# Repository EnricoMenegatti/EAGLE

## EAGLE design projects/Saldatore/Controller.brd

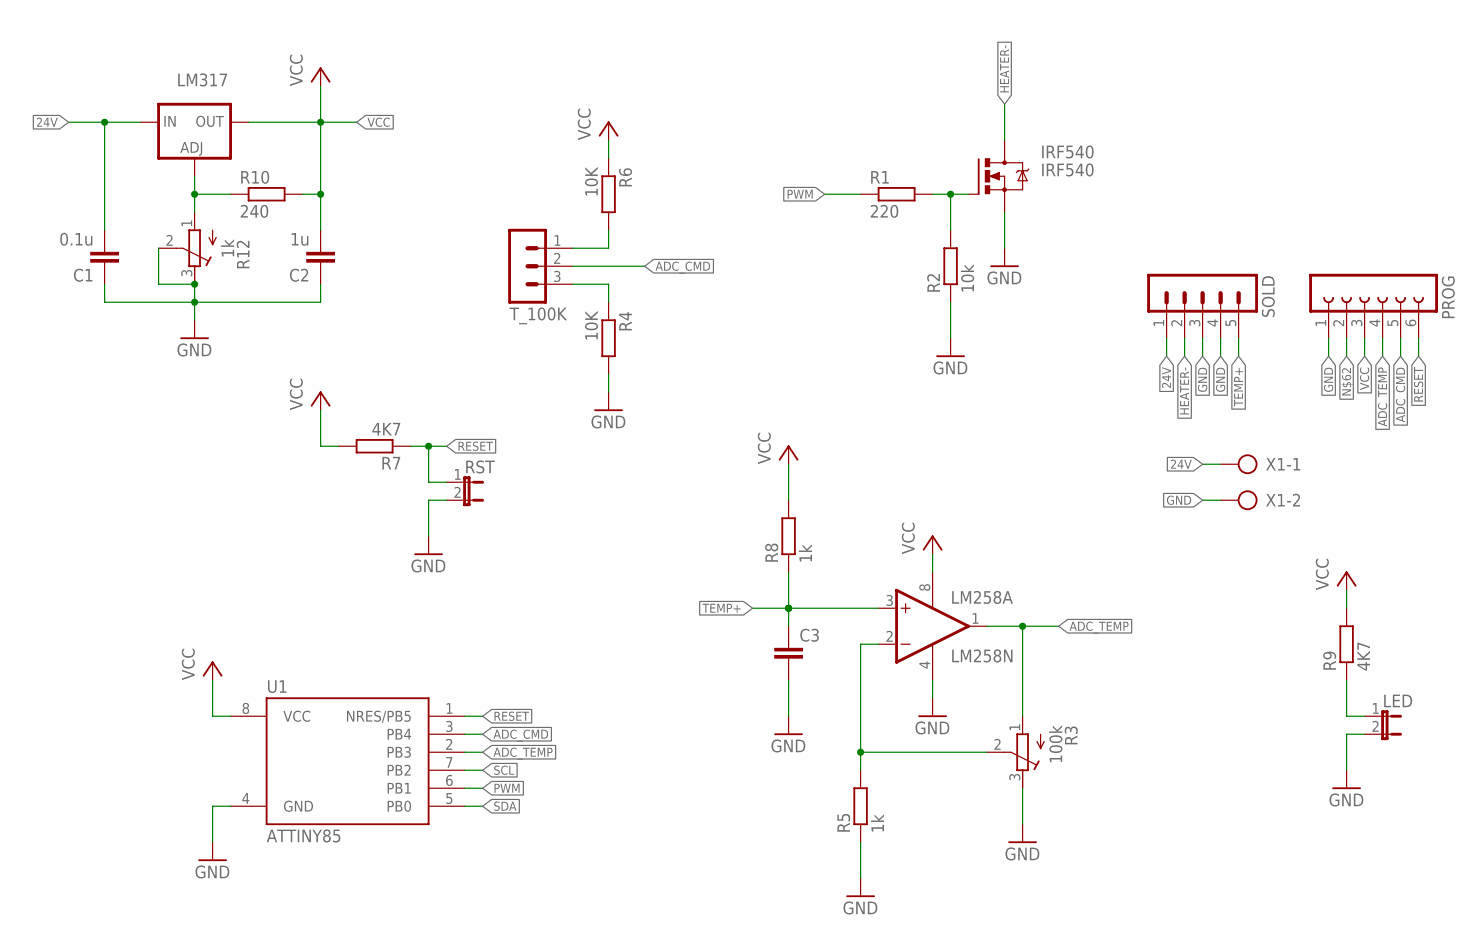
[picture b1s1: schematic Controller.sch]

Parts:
C1: 0.1u; C025-025X050
C2: 1u; C025-025X050
C3: C-EU025-025X050; C025-025X050
IRF540: IRF540; TO220BV
LED: JP1E; JP1
LM258: LM258N; DIL08
LM317: LM317TS; 317TS
PROG: FE06-1; FE06
R1: 220; 0204/7
R2: 10k; 0204/7
R3: 100k; RTRIM64W
R4: 10K; 0204V
R5, R8: 1k; 0204/7
R6: 10K; 0204/7
R7, R9: 4K7; 0204/7
R10: 240; 0204/7
R12: 1k; RTRIM64W
RST: JP1E; JP1
SOLD: MA05-1
T_100K: MA03-1
U1: ATTINY85; PDIP08_300MIL
X1: SMKDSP_1,5/2

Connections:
24V: C1.2, LM317.3 (IN), SOLD.1, X1.1
ADC_CMD: PROG.5, R6.2, T_100K.1, T_100K.2, U1.3 (PB4)
ADC_TEMP: LM258.1 (OUT), PROG.4, R3.1 (A), U1.2 (PB3)
GND: C1.1, C2.1, C3.2, IRF540.S, LED.2, LM258.4 (V-), PROG.1, R2.1, R3.3 (E), R4.2, R5.1, R12.2 (S), R12.3 (E), RST.2, SOLD.3, SOLD.4, U1.4 (GND), X1.2
HEATER-: IRF540.D, SOLD.2
unnamed: IRF540.G, R1.2, R2.2
unnamed: LM258.2 (-IN), R3.2 (S), R5.2
unnamed: LED.1, R9.1
unnamed: LM317.1 (ADJ), R10.1, R12.1 (A)
unnamed: R4.1, T_100K.3
PWM: R1.1, U1.6 (PB1)
RESET: PROG.6, R7.1, RST.1, U1.1 (NRES/PB5)
SCL: U1.7 (PB2)
SDA: U1.5 (PB0)
TEMP+: C3.1, LM258.3 (+IN), R8.1, SOLD.5
VCC: C2.2, LM258.8 (V+), LM317.2 (OUT), PROG.3, R6.1, R7.2, R8.2, R9.2, R10.2, U1.8 (VCC)

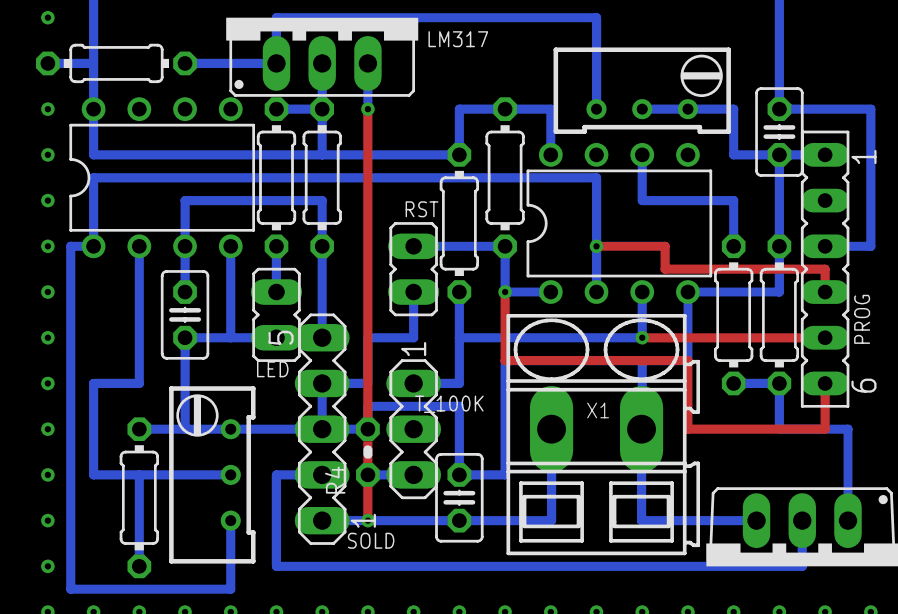
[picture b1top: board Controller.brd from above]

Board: 2 copper layers, 24 parts (0 on the bottom side), 14 nets.

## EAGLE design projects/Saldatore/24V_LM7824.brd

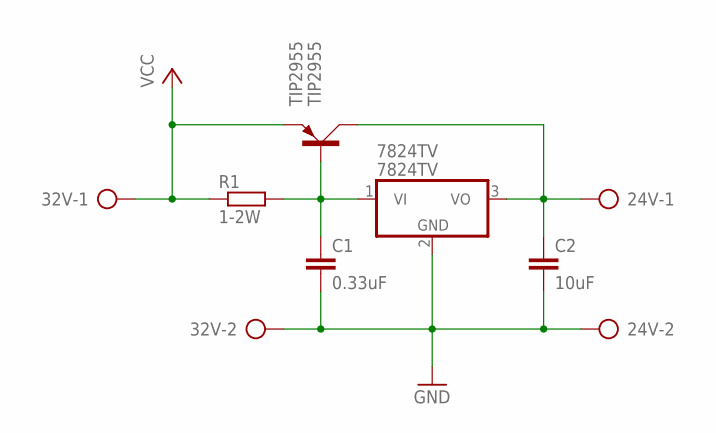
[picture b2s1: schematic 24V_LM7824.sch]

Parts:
24V, 32V: SMKDSP_1,5/2
7824TV: 7824TV; TO220V
C1: 0.33uF; C025-025X050
C2: 10uF; C025-025X050
R1: 1-2W; 0309/10
TIP2955: TIP2955; TOP3AV

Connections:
GND: 24V.2, 32V.2, 7824TV.2 (GND), C1.2, C2.2
unnamed: 7824TV.1 (VI), C1.1, R1.2, TIP2955.B
unnamed: 24V.1, 7824TV.3 (VO), C2.1, TIP2955.C
VCC: 32V.1, R1.1, TIP2955.E

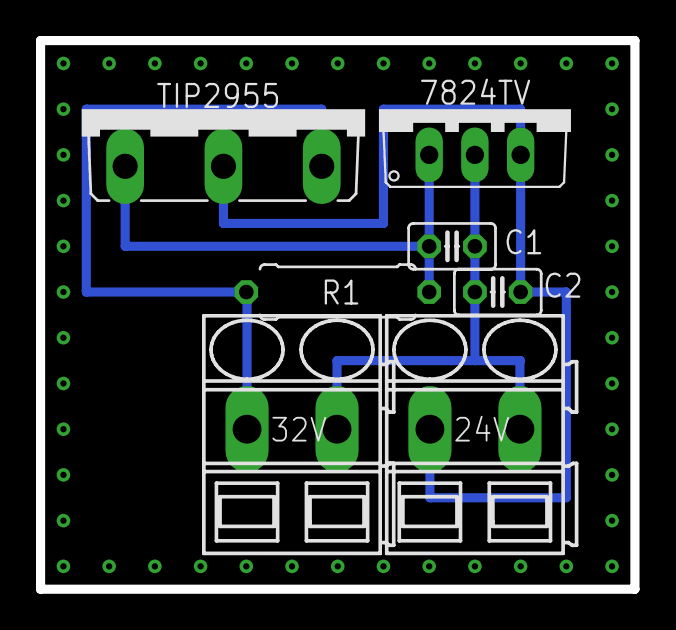
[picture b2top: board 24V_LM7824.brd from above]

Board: 2 copper layers, 33.0 x 30.5 mm, 7 parts (0 on the bottom side), 4 nets.

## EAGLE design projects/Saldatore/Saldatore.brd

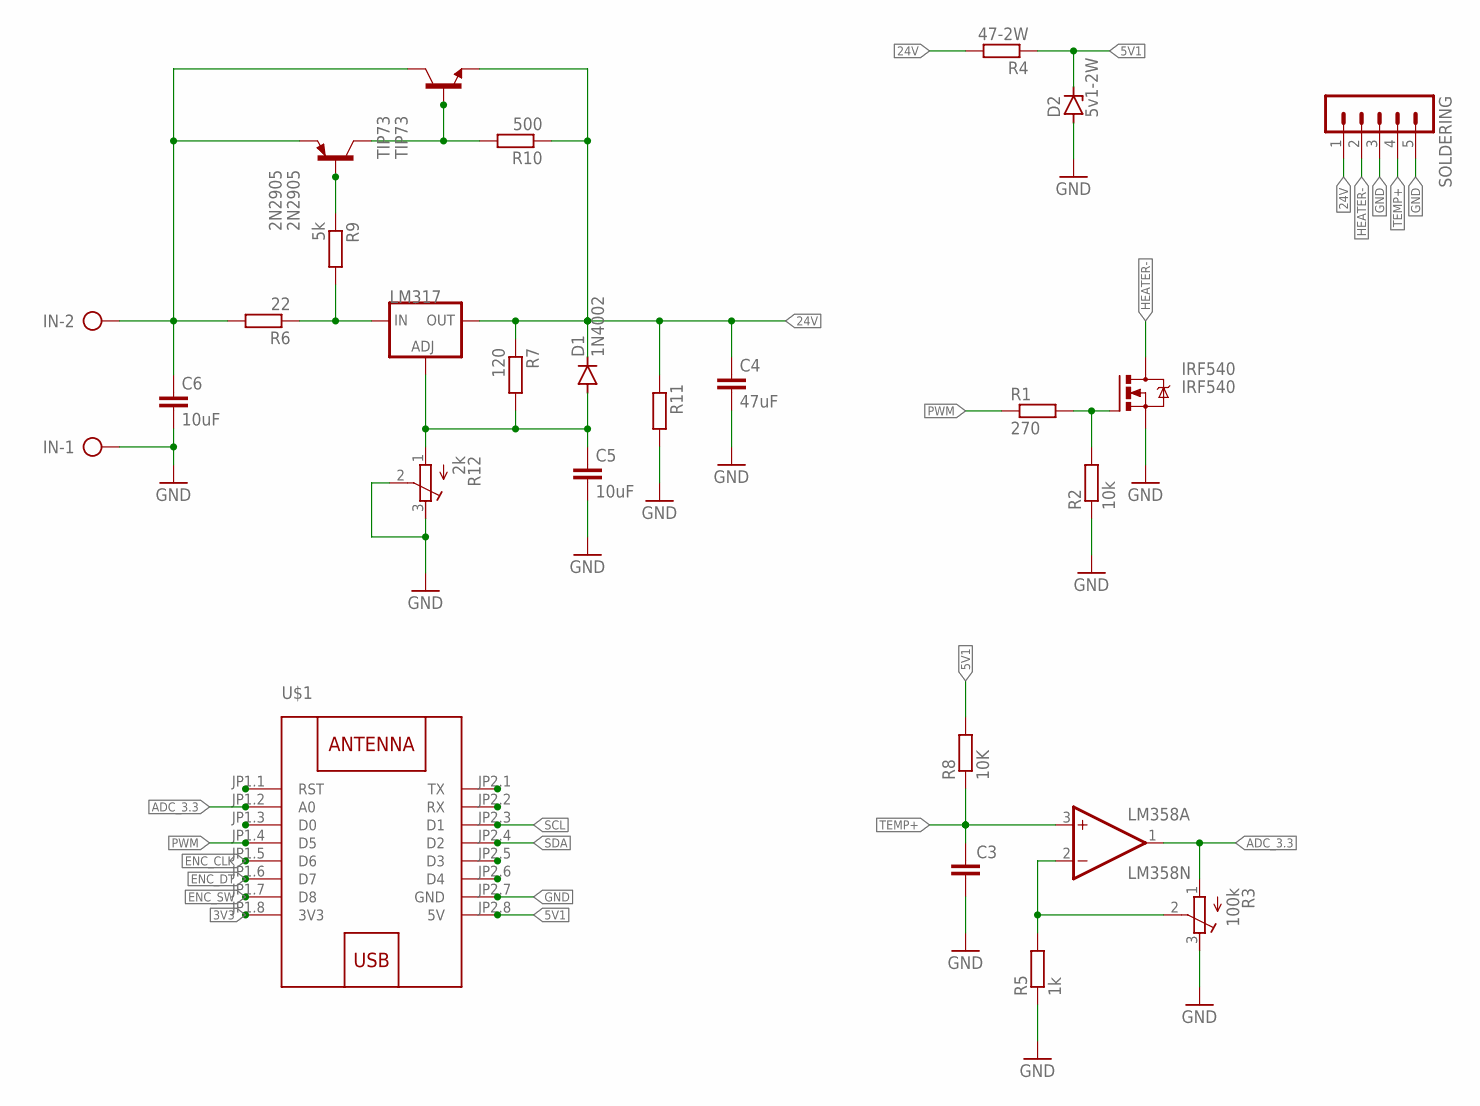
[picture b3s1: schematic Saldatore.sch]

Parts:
2N2905: 2N2905; TO39
C3: C-EU025-025X050; C025-025X050
C4: 47uF; C025-025X050
C5, C6: 10uF; C025-025X050
D1: 1N4002; DIOAD860W70L460D235B
D2: 5v1-2W; DO41Z10
IN: SMKDSP_1,5/2
IRF540: IRF540; TO220BV
LM317: LM317TS317TS_TO220; TO220V
LM358: LM358N; DIL08
R1: 270; 0204/7
R2: 10k; 0204/7
R3: 100k; RTRIM64W
R4: 47-2W; 0204/7
R5: 1k; 0204/7
R6: 22; 0204/7
R7: 120; 0204/7
R8: 10K; 0204/7
R9: 5k; 0204/7
R10: 500; 0204/7
R11: R-EU_0204/7; 0204/7
R12: 2k; RTRIM64W
SOLDERING: MA05-1
TIP73: TIP73; TO5
U$1: WEMOS-D1-MINI

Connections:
3V3: U$1.JP1.8 (3V3)
5V1: D2.C, R4.1, R8.2, U$1.JP2.8 (5V)
24V: C4.1, D1.1 (C), LM317.2 (OUT), R4.2, R7.1, R10.1, R11.1, SOLDERING.1, TIP73.1 (E)
ADC_3.3: LM358.1 (OUT), R3.1 (A), U$1.JP1.2 (A0)
ENC_CLK: U$1.JP1.5 (D6)
ENC_DT: U$1.JP1.6 (D7)
ENC_SW: U$1.JP1.7 (D8)
GND: C3.2, C4.2, C5.2, C6.2, D2.A, IN.1, IRF540.S, R2.1, R3.3 (E), R5.1, R11.2, R12.2 (S), R12.3 (E), SOLDERING.3, SOLDERING.5, U$1.JP2.7 (GND)
HEATER-: IRF540.D, SOLDERING.2
unnamed: IRF540.G, R1.2, R2.2
unnamed: LM358.2 (-IN), R3.2 (S), R5.2
unnamed: LM317.3 (IN), R6.1, R9.2
unnamed: 2N2905.2 (B), R9.1
unnamed: 2N2905.3 (C), R10.2, TIP73.2 (B)
unnamed: 2N2905.1 (E), C6.1, IN.2, R6.2, TIP73.3 (C)
unnamed: C5.1, D1.2 (A), LM317.1 (ADJ), R7.2, R12.1 (A)
PWM: R1.1, U$1.JP1.4 (D5)
SCL: U$1.JP2.3 (D1)
SDA: U$1.JP2.4 (D2)
TEMP+: C3.1, LM358.3 (+IN), R8.1, SOLDERING.4
V+: LM358.8 (V+)
V-: LM358.4 (V-)

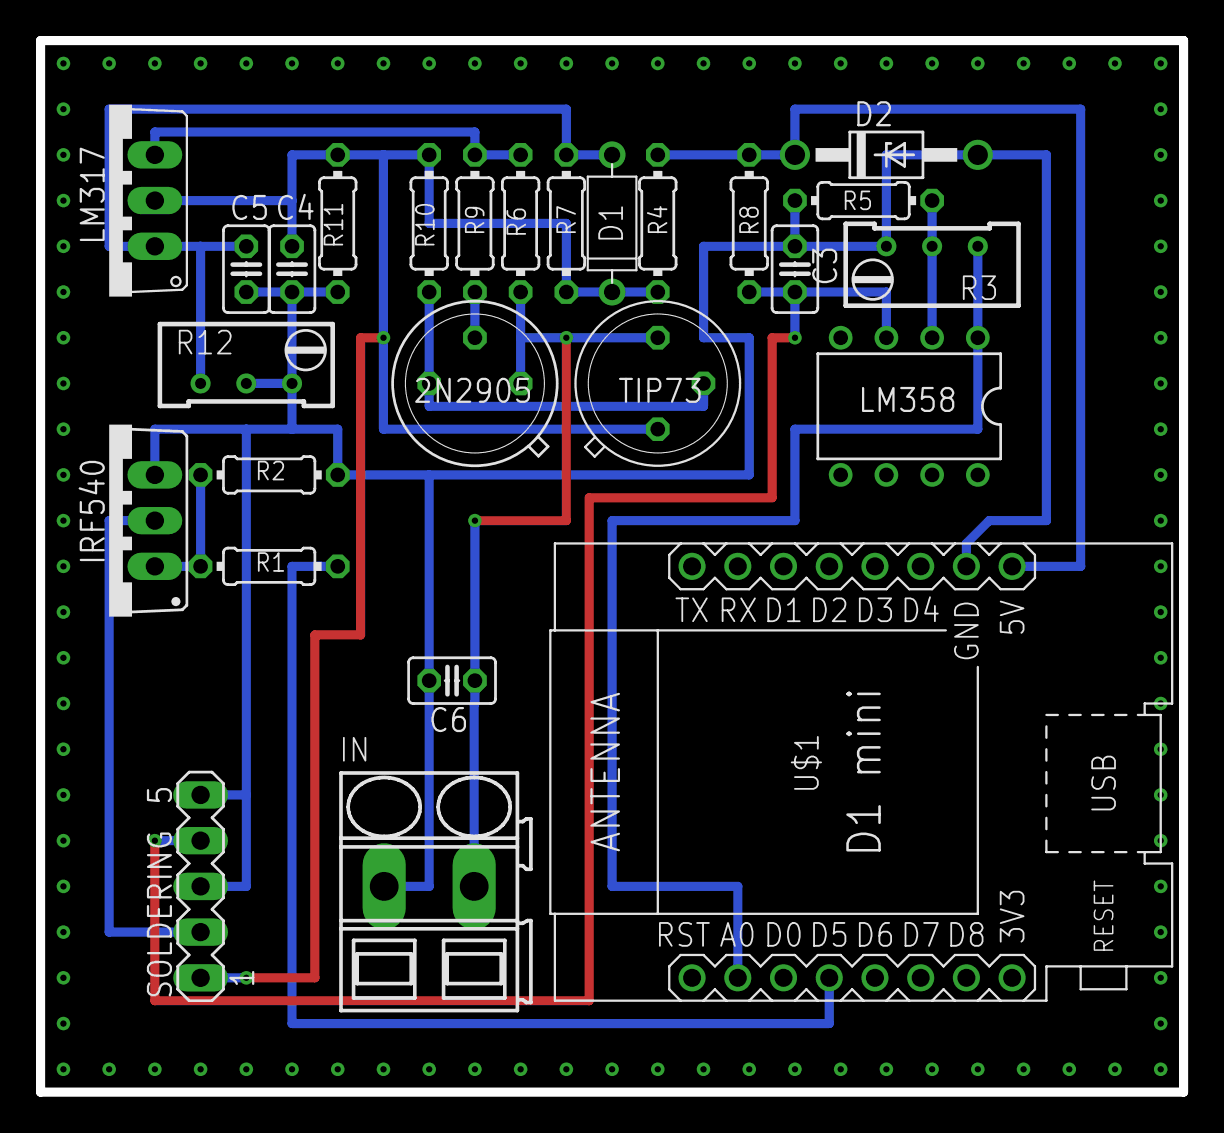
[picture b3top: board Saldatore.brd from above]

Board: 2 copper layers, 63.5 x 58.4 mm, 26 parts (0 on the bottom side), 14 nets.

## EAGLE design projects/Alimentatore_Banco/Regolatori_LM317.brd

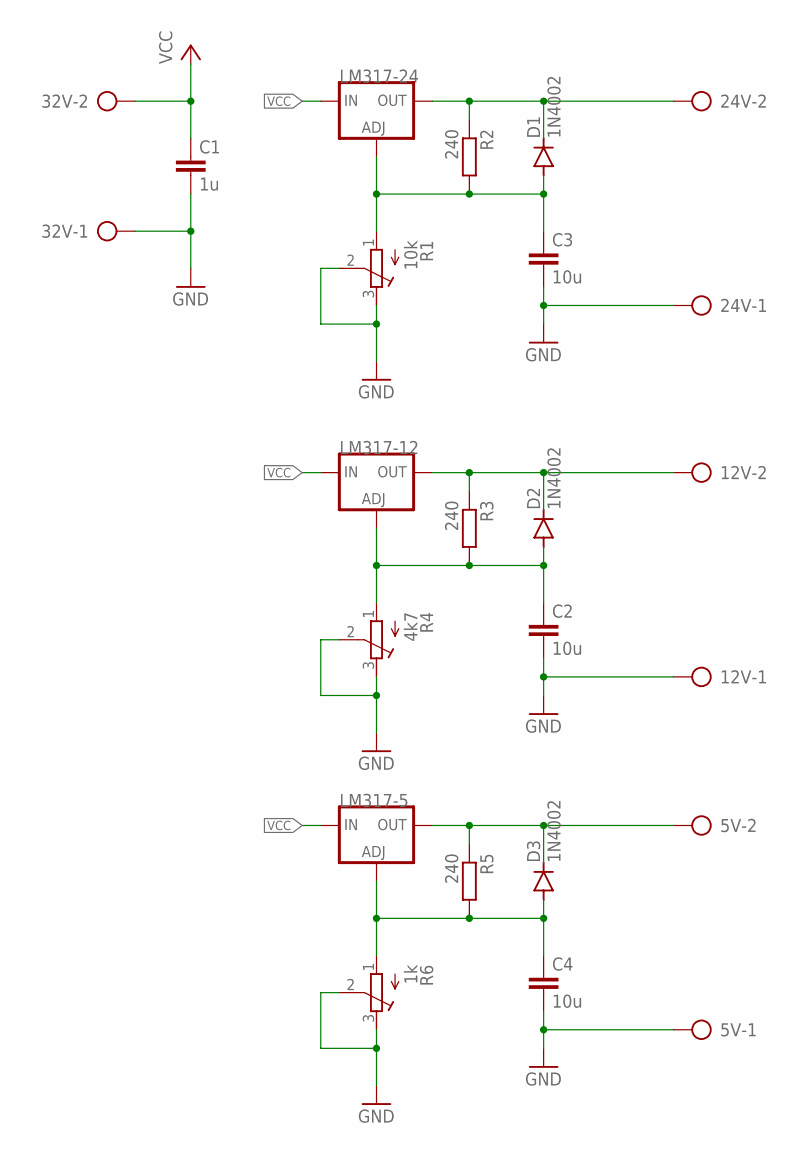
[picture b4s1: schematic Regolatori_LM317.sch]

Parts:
5V, 12V, 24V, 32V: SMKDSP_1,5/2
C1: 1u; C025-025X050
C2, C3, C4: 10u; C025-025X050
D1, D2, D3: 1N4002; DIOAD860W70L460D235B
LM317-5, LM317-12, LM317-24: LM317TS317TS_TO220; TO220V
R1: 10k; RTRIM64W
R2, R3, R5: 240; 0204/7
R4: 4k7; RTRIM64W
R6: 1k; RTRIM64W

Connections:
GND: 5V.1, 12V.1, 24V.1, 32V.1, C1.2, C2.2, C3.2, C4.2, R1.2 (S), R1.3 (E), R4.2 (S), R4.3 (E), R6.2 (S), R6.3 (E)
unnamed: 24V.2, D1.1 (C), LM317-24.2 (OUT), R2.1
unnamed: C2.1, D2.2 (A), LM317-12.1 (ADJ), R3.2, R4.1 (A)
unnamed: 12V.2, D2.1 (C), LM317-12.2 (OUT), R3.1
unnamed: C4.1, D3.2 (A), LM317-5.1 (ADJ), R5.2, R6.1 (A)
unnamed: 5V.2, D3.1 (C), LM317-5.2 (OUT), R5.1
unnamed: C3.1, D1.2 (A), LM317-24.1 (ADJ), R1.1 (A), R2.2
VCC: 32V.2, C1.1, LM317-5.3 (IN), LM317-12.3 (IN), LM317-24.3 (IN)

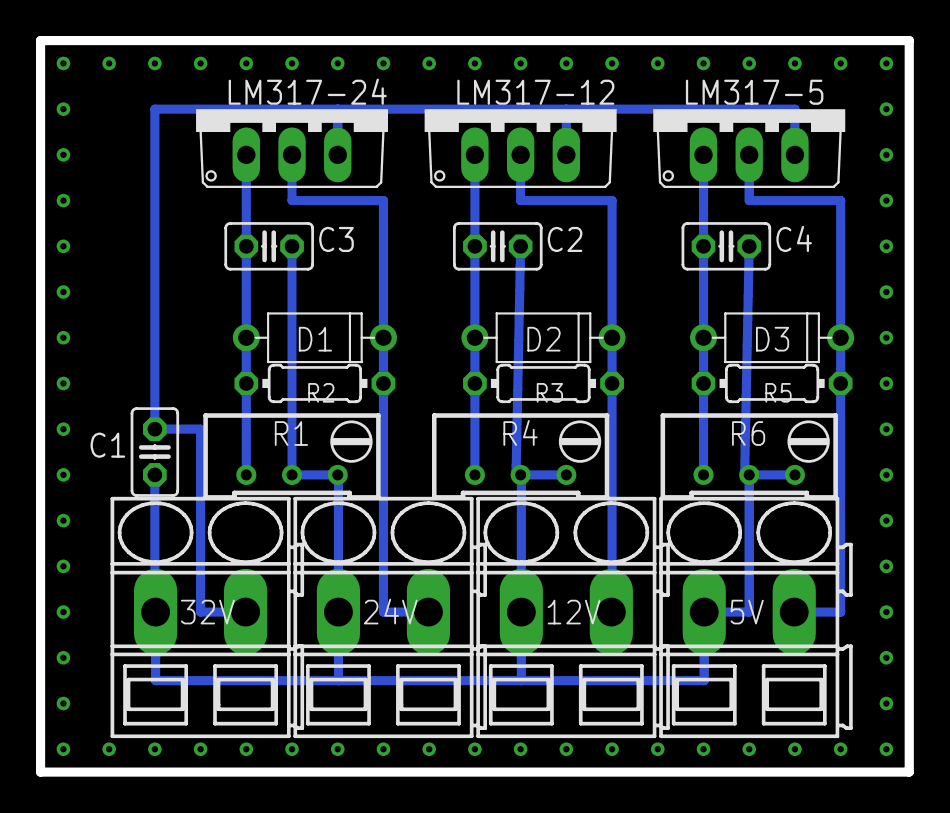
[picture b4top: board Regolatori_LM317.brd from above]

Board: 2 copper layers, 48.3 x 40.6 mm, 20 parts (0 on the bottom side), 8 nets.

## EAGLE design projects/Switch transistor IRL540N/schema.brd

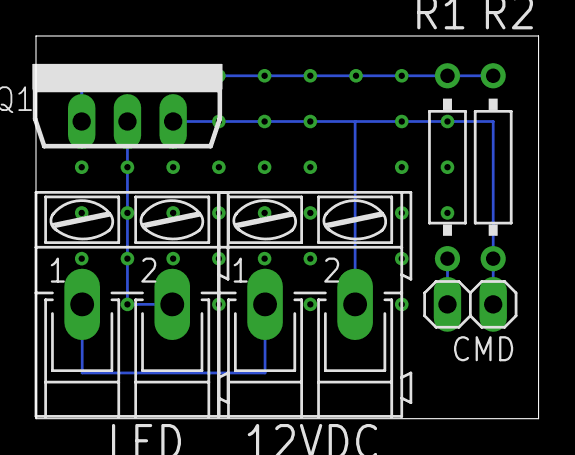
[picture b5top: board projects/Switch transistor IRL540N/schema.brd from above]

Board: 2 copper layers, 27.9 x 21.3 mm, 6 parts (0 on the bottom side), 5 nets.

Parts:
12VDC: AK300/2
CMD: 1X02
LED: AK300/2
Q1: IRL540N; TO262-V
R1: 270; RS1/4
R2: 10k; RS1/4

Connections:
GND: 12VDC.2, CMD.1, Q1.3, R2.1
unnamed: CMD.2, R1.1
unnamed: Q1.1, R1.2, R2.2
unnamed: 12VDC.1, LED.1
unnamed: LED.2, Q1.2

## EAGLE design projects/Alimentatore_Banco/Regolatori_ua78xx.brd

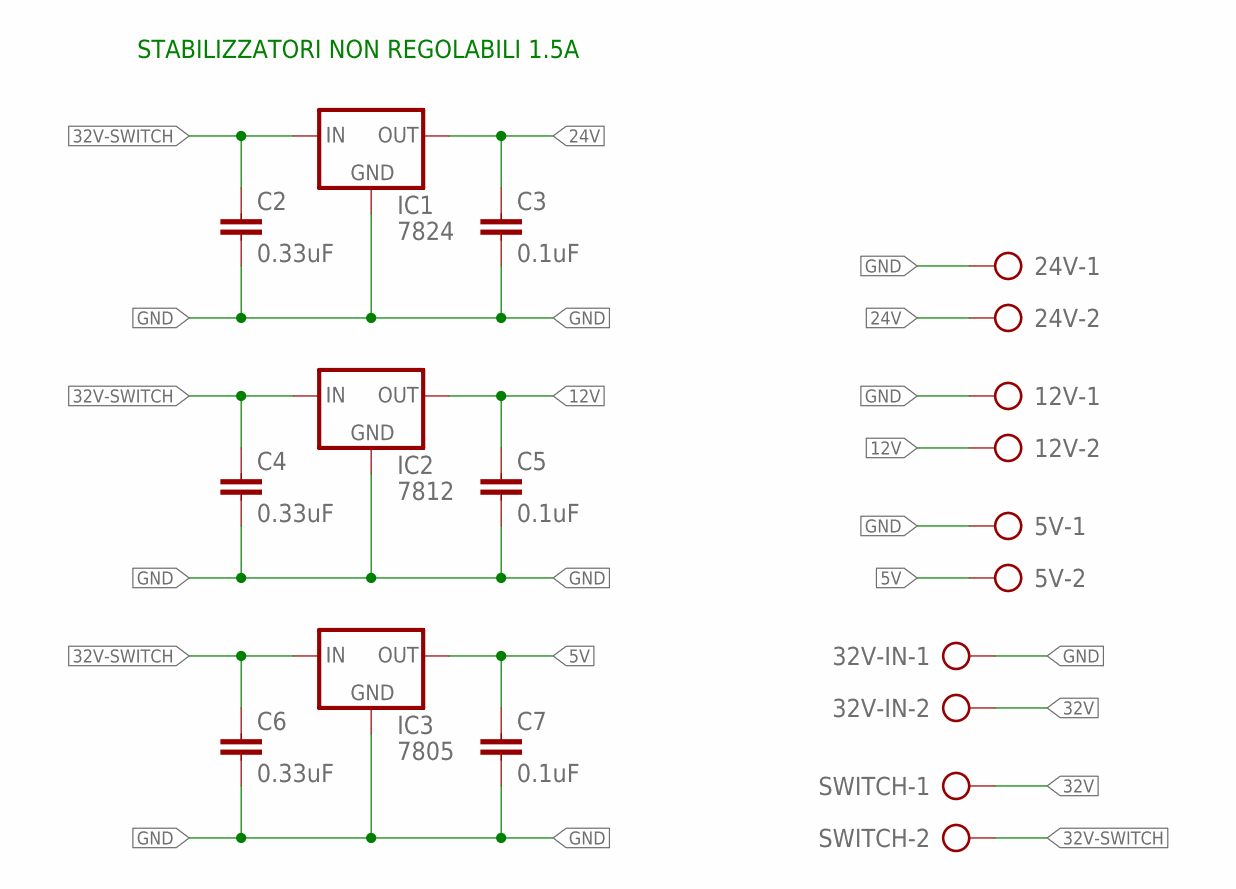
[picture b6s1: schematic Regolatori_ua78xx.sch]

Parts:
5V, 12V, 24V, 32V-IN: SMKDSP_1,5/2
C2, C4, C6: 0.33uF; C025-025X050
C3, C5, C7: 0.1uF; C025-025X050
IC1: 7824; 78XXS
IC2: 7812; 78XXS
IC3: 7805; 78XXS
SWITCH: SMKDSP_1,5/2

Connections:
5V: 5V.2, C7.1, IC3.OUT
12V: 12V.2, C5.1, IC2.OUT
24V: 24V.2, C3.1, IC1.OUT
32V: 32V-IN.2, SWITCH.1
32V-SWITCH: C2.1, C4.1, C6.1, IC1.IN, IC2.IN, IC3.IN, SWITCH.2
GND: 5V.1, 12V.1, 24V.1, 32V-IN.1, C2.2, C3.2, C4.2, C5.2, C6.2, C7.2, IC1.GND, IC2.GND, IC3.GND

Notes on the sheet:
STABILIZZATORI NON REGOLABILI 1.5A

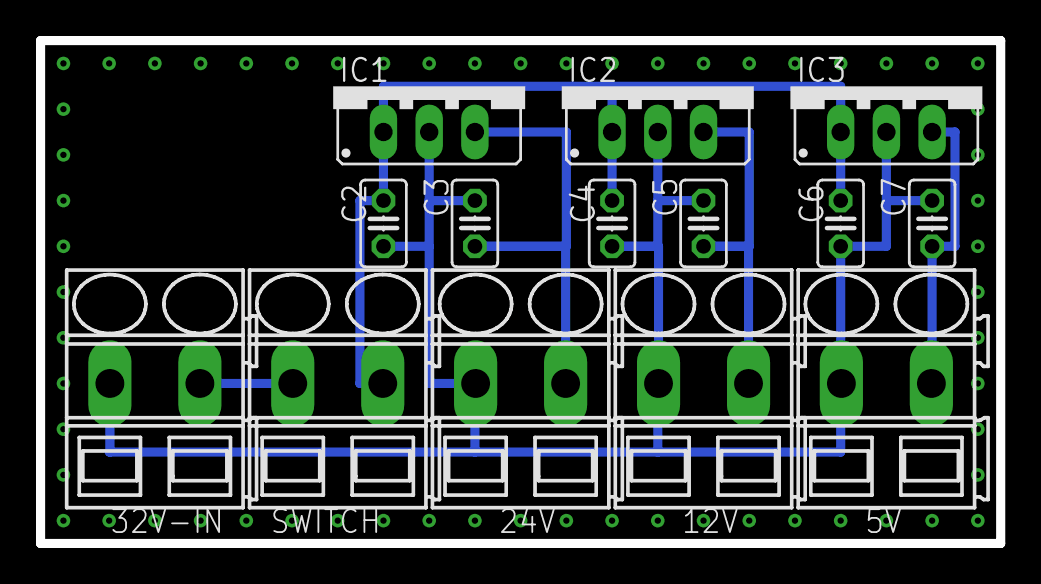
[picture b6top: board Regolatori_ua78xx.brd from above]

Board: 2 copper layers, 53.3 x 27.9 mm, 14 parts (0 on the bottom side), 6 nets.

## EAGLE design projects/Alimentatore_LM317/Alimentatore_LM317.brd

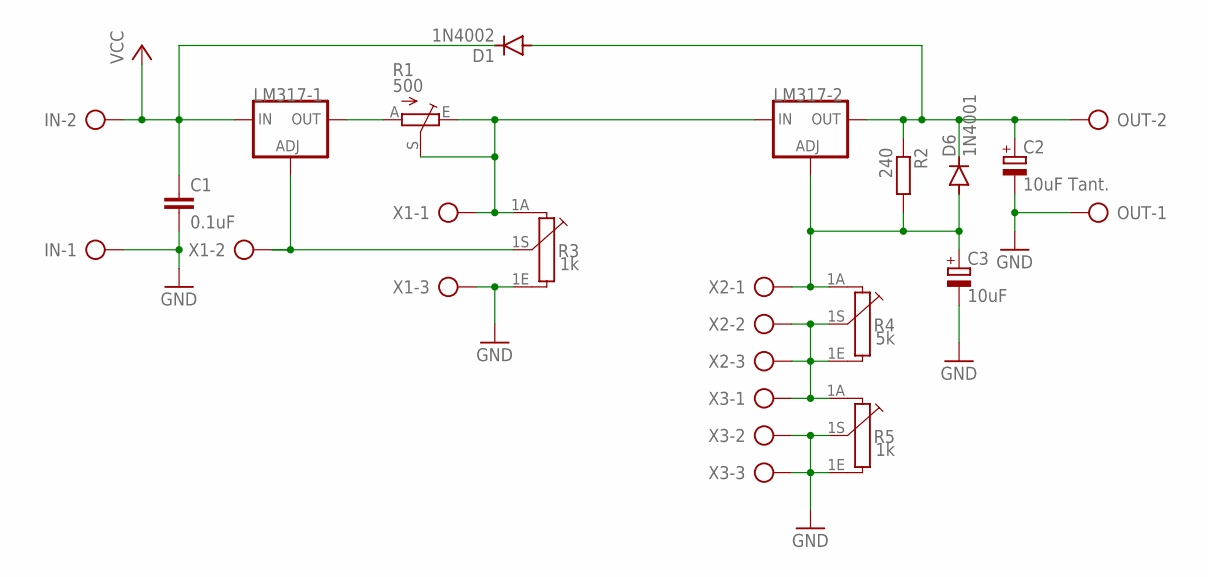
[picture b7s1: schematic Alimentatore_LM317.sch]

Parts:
C1: 0.1uF; C025-024X044
C2: 10uF Tant.; E2-5
C3: 10uF; E2-5
D1: 1N4002; DIOAD860W70L460D235B
D6: 1N4001; DIOAD860W70L460D235B
IN: SMKDSP_1,5/2
LM317-1, LM317-2: LM317TS317TS_TO220; TO220V
OUT: SMKDSP_1,5/2
R1: 500; CA6V
R2: 240; 0204/7
R3, R5: 1k; PC16S
R4: 5k; PC16S
X1, X2, X3: SMKDSP_1,5/3

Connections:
GND: C1.2, C2.-, C3.-, IN.1, OUT.1, R3.1E, R5.1E, R5.1S, X1.3, X3.2, X3.3
unnamed: C2.+, D1.2 (A), D6.1 (C), LM317-2.2 (OUT), OUT.2, R2.1
unnamed: LM317-1.2 (OUT), R1.A
unnamed: LM317-2.3 (IN), R1.E, R1.S, R3.1A, X1.1
unnamed: R4.1E, R4.1S, R5.1A, X2.2, X2.3, X3.1
unnamed: LM317-1.1 (ADJ), R3.1S, X1.2
unnamed: C3.+, D6.2 (A), LM317-2.1 (ADJ), R2.2, R4.1A, X2.1
VCC: C1.1, D1.1 (C), IN.2, LM317-1.3 (IN)

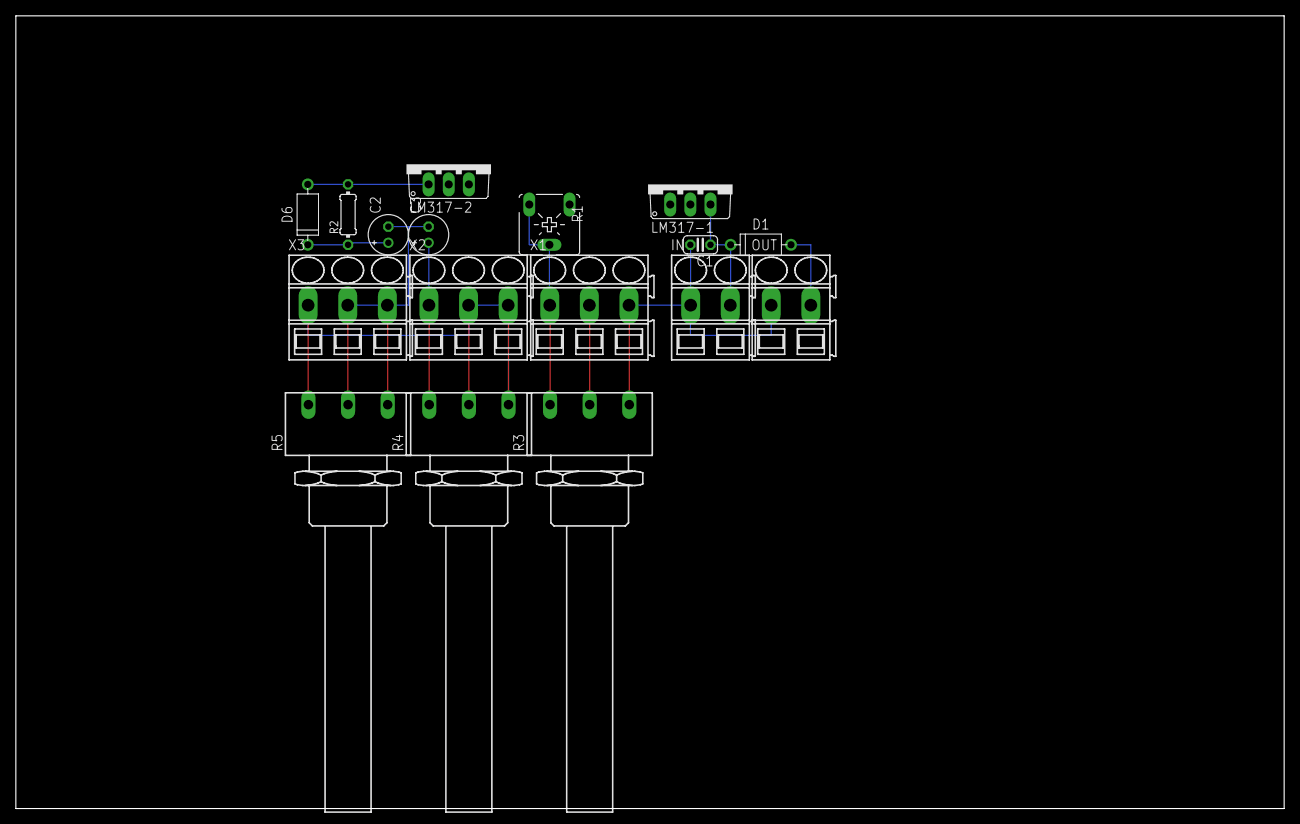
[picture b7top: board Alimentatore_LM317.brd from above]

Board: 2 copper layers, 160.0 x 100.0 mm, 17 parts (0 on the bottom side), 8 nets.

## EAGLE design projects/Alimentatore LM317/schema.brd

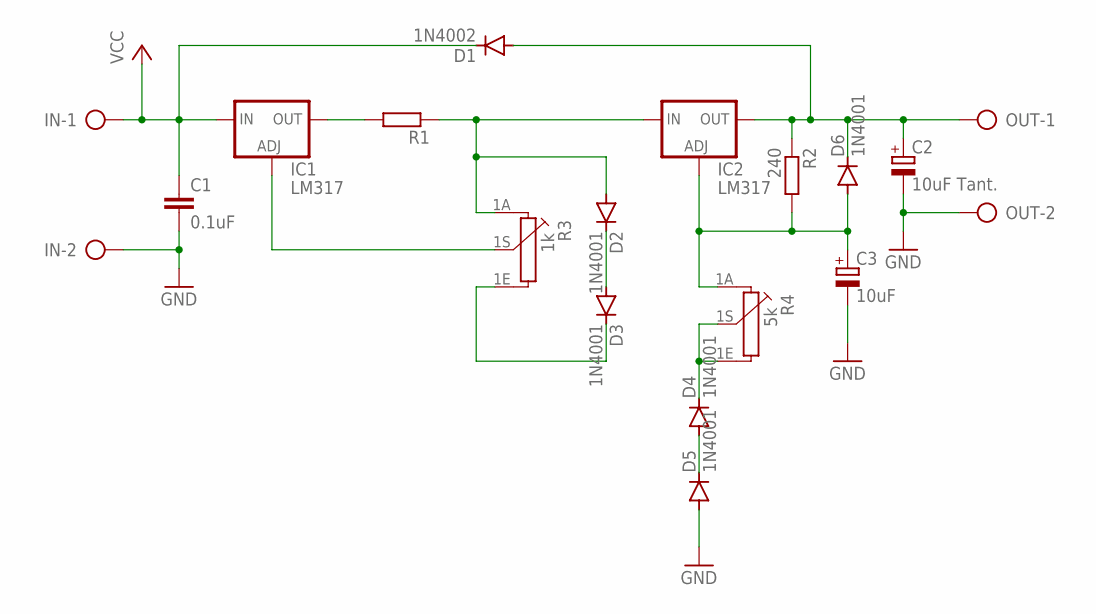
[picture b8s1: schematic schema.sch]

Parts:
C1: 0.1uF; C025-024X044
C2: 10uF Tant.; E2-5
C3: 10uF; E2-5
D1: 1N4002; DO41-10
D2, D3, D4, D5, D6: 1N4001; DO41-10
IC1, IC2: LM317; 317TS
IN: SMKDSP_1,5/2
OUT: SMKDSP_1,5/2
R1: R-EU_0204/7; 0204/7
R2: 240; 0204/7
R3: 1k; PC16S
R4: 5k; PC16S

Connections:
GND: C1.2, C2.-, C3.-, D5.A, IN.2, OUT.2
unnamed: C2.+, D1.A, D6.C, IC2.2 (OUT), OUT.1, R2.1
unnamed: IC1.2 (OUT), R1.2
unnamed: D2.A, IC2.3 (IN), R1.1, R3.1A
unnamed: D2.C, D3.A
unnamed: IC1.1 (ADJ), R3.1S
unnamed: D4.A, D5.C
unnamed: D3.C, R3.1E
unnamed: C3.+, D6.A, IC2.1 (ADJ), R2.2, R4.1A
unnamed: D4.C, R4.1E, R4.1S
VCC: C1.1, D1.C, IC1.3 (IN), IN.1

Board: 2 copper layers, 17 parts (0 on the bottom side), 11 nets, no tracks yet.

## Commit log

2019-09-12 progetto switch mosfet.
2019-09-12 rinominato progetto switch.
2019-09-12 in lavoro alimentatore
2019-09-17 terminato primo schema alimentatore lm317
2019-09-17 creata seconda versione della scheda. esportate immagini.
2019-09-17 aggiornata immagine scheda.
2019-09-20 aggiunti circuiti alternativi LM317.
2019-09-20 divise schemi alimentatore da banco
2019-09-30 terminato schema regolatori.
2019-09-30 rimossi file temporanei
2019-09-30 rimossi file temporanei.
2019-09-30 in lavoro saldatore.
2019-10-01 in lavoro messa su scheda saldatore.
2019-10-02 terminato schema saldatore. esportate immagini.
2019-10-02 immagine per montaggio.
2019-10-03 diviso progetto saldatore su due schede.
2019-10-07 creata part list saldatore.
2019-11-24 aggiornato saldatore.
2019-11-25 commit da controllare su Inspiron17.
2019-11-26 in lavoro immagine scheda controller.
2020-01-09 aggiornato controller
2020-01-28 aggiornata configurazione potenziometro di comando.

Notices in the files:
parts and their libraries:
diy-modules: Released under the Creative Commons Attribution 4.0 International License: http://creativecommons.org/licenses/by/4.0
